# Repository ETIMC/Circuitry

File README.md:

# Structure
## Components
This folder contains symbols, footprints and STEP files for components used in the circuits that are not in the default libraries of Kicad.

## Controller
This folder contains the Kicad project for the *Controller* circuit.

## Host
This folder contains the Kicad project for the *Host* circuit.

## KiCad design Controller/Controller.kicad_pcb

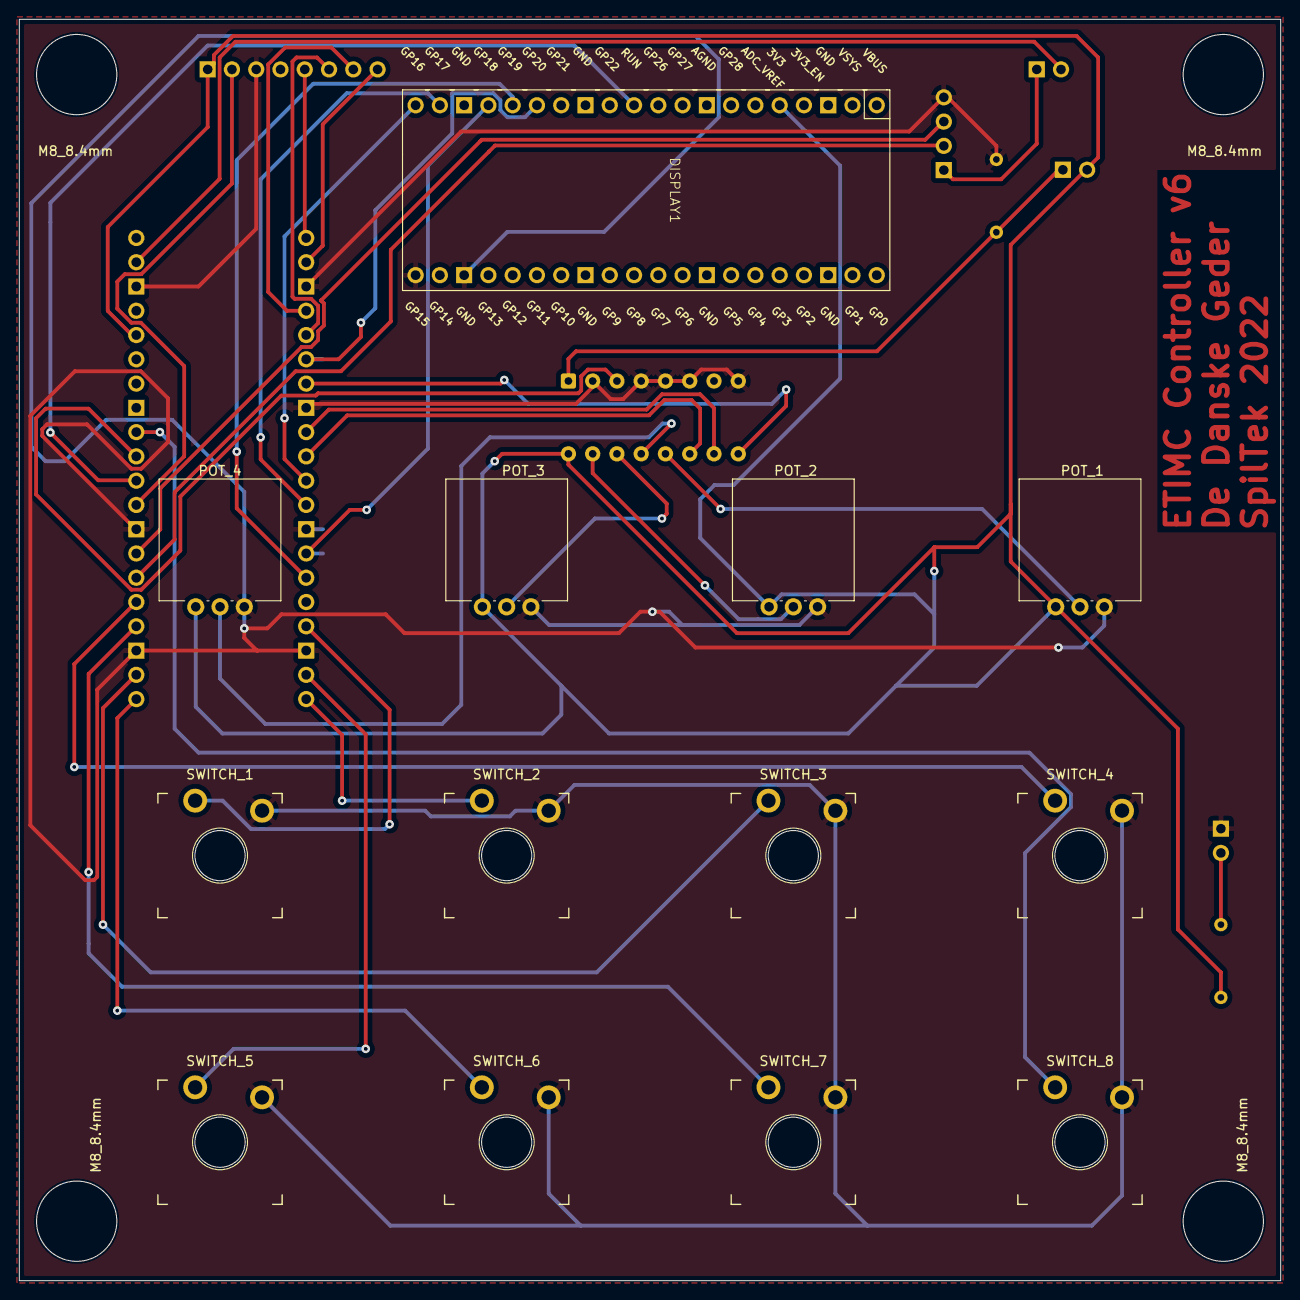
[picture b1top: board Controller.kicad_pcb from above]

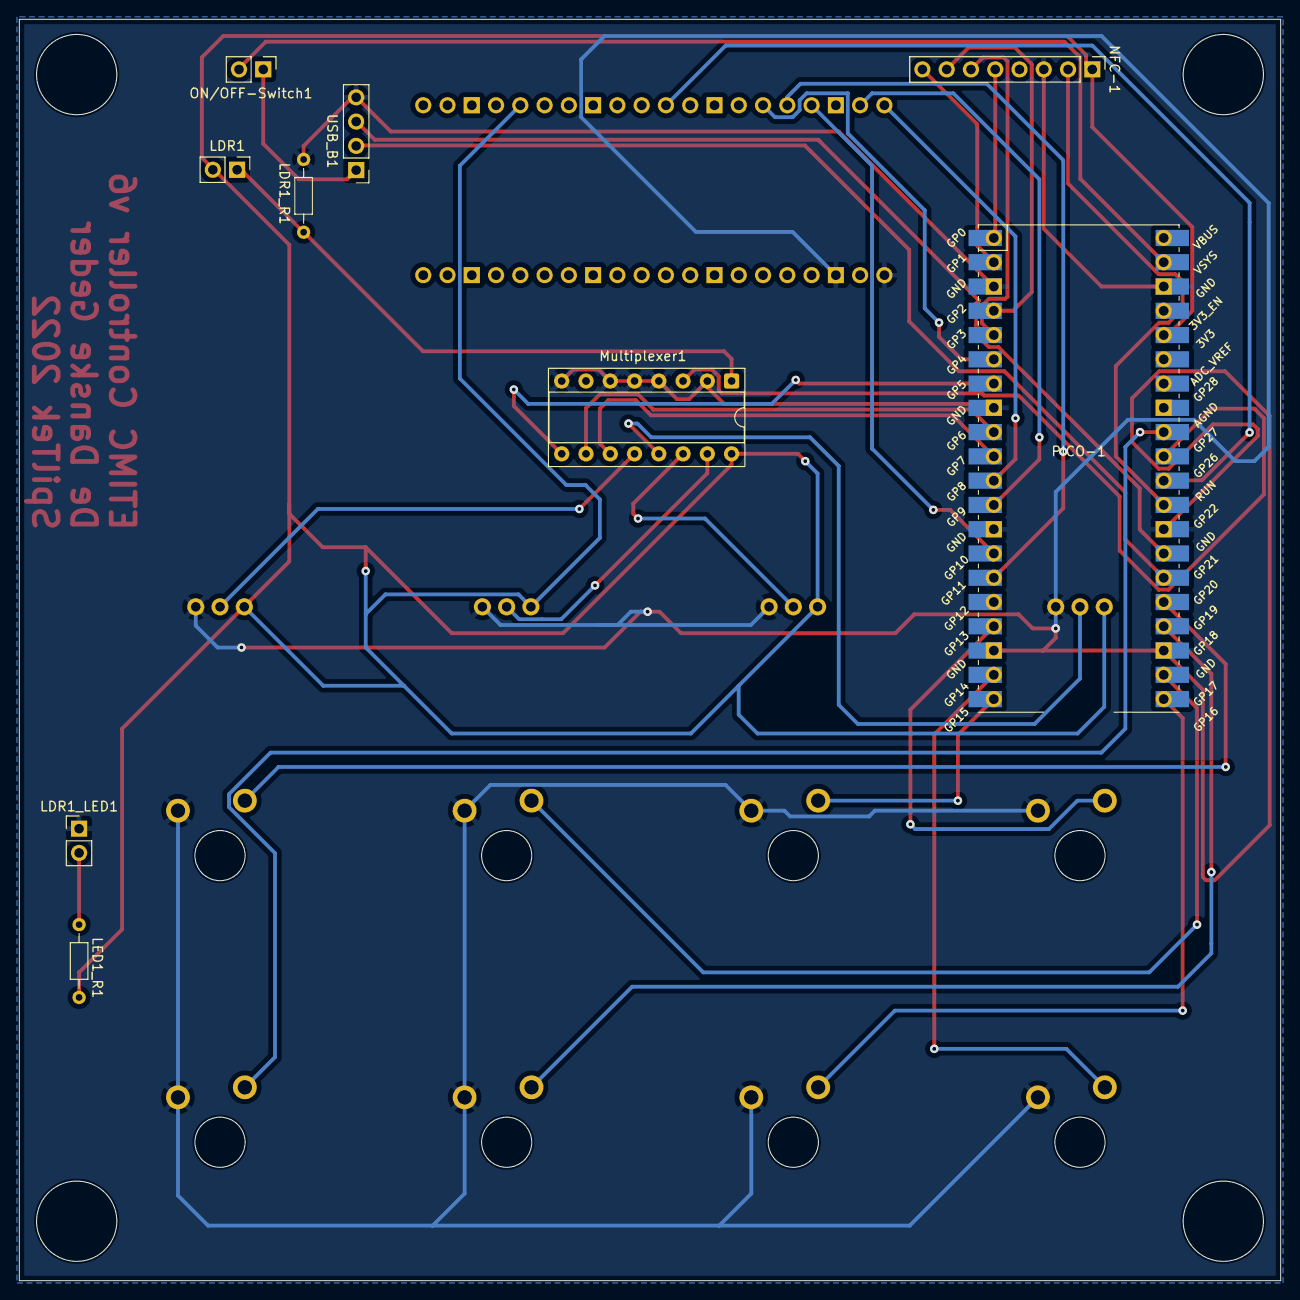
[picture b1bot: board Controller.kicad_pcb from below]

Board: 2 copper layers, 132.0 x 132.0 mm, 26 parts (9 on the bottom side), 35 nets.

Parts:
DISPLAY1: display-footprint
LDR1: LDR03; PinHeader_1x02_P2.54mm_Vertical
LDR1_LED1: RED; PinHeader_1x02_P2.54mm_Vertical
LDR1_R1: ???; R_Axial_DIN0204_L3.6mm_D1.6mm_P7.62mm_Horizontal
LED1_R1: 120; R_Axial_DIN0204_L3.6mm_D1.6mm_P7.62mm_Horizontal
MOUNTING_HOLE_1, MOUNTING_HOLE_2, MOUNTING_HOLE_3, MOUNTING_HOLE_4: M8_8.4mm; MountingHole_8.4mm_M8_ETIMC
Multiplexer1: 74HC4051; DIP-16_W7.62mm_Socket
NFC-1: RC522; PinHeader_1x08_P2.54mm_Vertical
ON/OFF-Switch1: KCD1-101; PinHeader_1x02_P2.54mm_Vertical
PICO-1: RASPBERRY_PI_PICO_W; pico-footprint
POT_1, POT_2, POT_3, POT_4: R_Potentiometer; Potentiometer_Vishay_148-149_Single_Vertical
SWITCH_1, SWITCH_2, SWITCH_3, SWITCH_4, SWITCH_5, SWITCH_6, SWITCH_7, SWITCH_8: SW_Push; SW_Gateron_LowProfile_HotSwap_THT (1)
USB_B1: USB_B; PinHeader_1x04_P2.54mm_Vertical

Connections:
3V3: DISPLAY1.36 (3V3), LDR1.2, LED1_R1.2, Multiplexer1.16 (VCC), NFC-1.1 (VCC), PICO-1.36 (3V3_OUT), POT_1.3, POT_2.3, POT_3.3, POT_4.3
+5V: ON/OFF-Switch1.2 (B), PICO-1.39 (VSYS)
GND: DISPLAY1.18 (GND), DISPLAY1.20 (SWY), LDR1_LED1.1 (K), LDR1_R1.1, Multiplexer1.2 (A6), Multiplexer1.4 (A7), Multiplexer1.5 (A5), Multiplexer1.6 (~E), Multiplexer1.8 (GND), NFC-1.3 (GND), PICO-1.3 (GND), PICO-1.8 (GND), PICO-1.13 (GND), PICO-1.18 (GND), PICO-1.23 (GND), PICO-1.28 (GND), PICO-1.38 (GND), POT_1.1, POT_2.1, POT_3.1, POT_4.1, SWITCH_1.2, SWITCH_2.2, SWITCH_3.2, SWITCH_4.2, SWITCH_5.2, SWITCH_6.2, SWITCH_7.2, SWITCH_8.2, USB_B1.4 (GND)
GP20: PICO-1.26 (I2C0_SDA/GP20), USB_B1.2 (D-)
GP21: PICO-1.27 (12C0_SCL/GP21), USB_B1.3 (D+)
GP22: NFC-1.2 (RST), PICO-1.29 (GP22)
unnamed: DISPLAY1.26 (BACKLIGHT_EN), PICO-1.6 (UART1_TX/I2C0_SDA/SPI0_RX/GP4)
unnamed: DISPLAY1.22 (LCD_CS), PICO-1.12 (UART1_RX/I2C0_SCL/SPI1_CSN/GP9)
unnamed: DISPLAY1.21 (LCD_DC), PICO-1.11 (UART1_TX/I2C0_SDA/SPI1_RX/GP8)
unnamed: DISPLAY1.25 (LCD_MOSI), PICO-1.15 (I2C1_SCL/SPI1_TX/GP11)
unnamed: DISPLAY1.24 (LCD_SCLK), PICO-1.14 (I2C1_SDA/SPI1_SCK/GP10)
unnamed: DISPLAY1.30 (RESET), PICO-1.30 (~RUN)
unnamed: LDR1_LED1.2 (A), LED1_R1.1
unnamed: Multiplexer1.13 (A0), POT_4.2
unnamed: Multiplexer1.14 (A1), POT_3.2
unnamed: Multiplexer1.15 (A2), POT_2.2
unnamed: Multiplexer1.12 (A3), POT_1.2
unnamed: LDR1.1, LDR1_R1.2, Multiplexer1.1 (A4)
unnamed: Multiplexer1.11 (S0), PICO-1.10 (I2C1_SCL/SPI0_TX/GP7)
unnamed: Multiplexer1.10 (S1), PICO-1.9 (I2C1_SDA/SPI0_SCK/GP6)
unnamed: Multiplexer1.9 (S2), PICO-1.7 (UART1_RX/I2C0_SCL/SPI0_CSN/GP5)
unnamed: NFC-1.5 (MISO/SCL/TX), PICO-1.1 (UART0_TX/I2C0_SDA/SPI0_RX/GP0)
unnamed: NFC-1.6 (MOSI), PICO-1.5 (I2C1_SCL/SPI0_TX/GP3)
unnamed: NFC-1.7 (SCK), PICO-1.4 (I2C1_SDA/SPI0_SCK/GP2)
unnamed: NFC-1.8 (SS/SDA/RX), PICO-1.2 (UART0_RX/I2C0_SCL/SPI0_CSN/GP1)
unnamed: ON/OFF-Switch1.1 (A), USB_B1.1 (VBUS)
unnamed: PICO-1.32 (I2C1_SCL/ADC1/GP27), SWITCH_8.1
unnamed: PICO-1.25 (I2C1_SCL/SPI0_TX/GP19), SWITCH_4.1
unnamed: PICO-1.20 (I2C1_SCL/SPI1_TX/GP15), SWITCH_2.1
unnamed: PICO-1.24 (I2C1_SDA/SPI0_SCK/GP18), SWITCH_7.1
unnamed: PICO-1.19 (I2C1_SDA/SPI1_SCK/GP14), SWITCH_5.1
unnamed: PICO-1.22 (UART0_RX/I2C0_SCL/SPI0_CSN/GP17), SWITCH_3.1
unnamed: PICO-1.17 (UART0_RX/I2C0_SCL/SPI1_CSN/GP13), SWITCH_1.1
unnamed: PICO-1.21 (UART0_TX/I2C0_SDA/SPI0_RX/GP16), SWITCH_6.1
POTS: Multiplexer1.3 (A), PICO-1.31 (I2C1_SDA/ADC0/GP26)

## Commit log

2025-03-13 Add LEDs and fix button pull up resistors
2025-03-13 Reorder level shifter
2025-03-13 Add sections
2025-03-19 Add schematic
2025-03-19 Edit symbols and add screen to schematic
2025-03-28 Add mosfet definition
2025-03-29 Add updated schematic PDF
2025-04-09 Rewire display
2025-04-23 Add components and lign up PCB
2025-04-25 PCB Routing
2025-04-25 Update PCB
2025-04-28 Fix i2c
2025-04-30 Fix the pcb
2025-04-30 Export gerber
2025-05-05 Fix mistakes
2025-05-12 Update schematic and schematic PDF
2025-05-12 Rename schematics and add png schematic
2025-05-13 Update PRL file for Kicad 9
